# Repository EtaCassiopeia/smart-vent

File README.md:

# smart-vent

Per-room HVAC vent control. Each vent has a small XIAO ESP32-C6 board driving an SG90
hobby servo that opens or closes a louver. The board joins a Thread mesh hosted by a
Raspberry Pi and exposes itself as a Matter **Window Covering** device. Home Assistant
runs on the same Pi and is the user-facing controller — you toggle the vent in the HA UI
or in a HA automation, and the command travels over Matter-over-Thread to the device,
which moves the servo.

The project is **Matter-over-Thread only**. There is no Wi-Fi path on the device, and no
cloud dependency. The Pi is the entire backend.

## Hardware

| Role | Part | Notes |
|------|------|-------|
| Hub | Raspberry Pi (any model with USB) | Runs three Docker containers: OTBR, matter-server, Home Assistant |
| Thread radio | SMLIGHT SLZB-07 USB dongle | CP210x USB-UART (`10c4:ea60`), enumerates as `/dev/ttyUSB0`. Used by OTBR as the Thread Radio Co-Processor |
| Vent MCU | Seeed XIAO ESP32-C6 | RISC-V chip with built-in 802.15.4 and BLE radios. Enumerates as `/dev/ttyACM0` (`303a:1001`) when plugged **directly** into the Pi — not through a USB hub |
| Actuator | SG90 servo | Signal on GPIO2 (XIAO D2 pin). 90° = vent closed, 180° = vent open |

## Architecture at a glance

```
   ┌─────────────────────── Raspberry Pi ──────────────────────────┐
   │                                                                │
   │  Home Assistant ── (WebSocket) ──► matter-server               │
   │       (:8123)                       (:5580)                    │
   │                                        │ BLE pairing           │
   │                                        ▼                       │
   │                                     BlueZ ─── (host BT)        │
   │                                        │                       │
   │                                        │ Matter ops over IPv6  │
   │                                        ▼                       │
   │                                     OTBR (OpenThread Border    │
   │                                           Router container)    │
   │                                        │                       │
   │                                        │ Thread (802.15.4)     │
   └────────────────────────────────────────┼───────────────────────┘
                                            │  ▲
                                  via SLZB-07 USB dongle
                                            │  │
                              ┌─────────────▼──┴────────────┐
                              │   XIAO ESP32-C6 (vent N)    │
                              │   Rust firmware + esp-matter│
                              │   GPIO2 ─► SG90 servo       │
                              └─────────────────────────────┘
```

## Where to look

- **[docs/handbook.md](docs/handbook.md)** — what the system is, how it works, why
  it's built the way it is. Read this top-to-bottom once. Covers Matter, Thread,
  the Pi services, the firmware internals, what happens during commissioning and
  on every replug.
- **[docs/dev-setup.md](docs/dev-setup.md)** — what to install on your own dev
  machine (Linux x86_64 recommended, Pi for deployment/validation, macOS as
  a secondary option) before touching firmware, the SD image, the Pi hub
  stack, the provisioning CLI, or the PCB tooling.
- **[docs/runbook.md](docs/runbook.md)** — step-by-step procedures for **developers**.
  How to set up the Pi from scratch, build the firmware, flash a new vent, commission
  it via HA, assign it to a room. Plus a symptom-driven troubleshooting matrix.
- **[docs/provider-runbook.md](docs/provider-runbook.md)** — step-by-step for
  **providers** assembling kits to ship to clients. Uses the
  `smart-vent-provision` CLI end-to-end: bake the SD card, flash + capture N
  vents, print stickers + quick-start, pack and ship. No source builds.
- **[docs/mobile-api.md](docs/mobile-api.md)** — API contract the smart-vent mobile
  app builds against (matter-server WS, HA REST, mDNS).
- **[docs/mobile-app-spec.md](docs/mobile-app-spec.md)** — screen-by-screen spec
  the Flutter team works from.

## Repo layout

```
firmware/
  vent-controller/                 ESP32-C6 firmware (Rust + ESP-IDF v5.2.3)
    src/                           Rust modules: main, matter, servo, state, identity, ...
    components/esp_matter_bridge/  C++ shim over esp-matter SDK
    sdkconfig.defaults             Non-default ESP-IDF kconfig
    partitions.csv                 nvs / phy_init / 3 MB factory app layout
  shared-protocol/                 vent-protocol crate (CBOR types, angle constants)
docs/
  handbook.md                      Conceptual reference
  runbook.md                       Step-by-step procedures
homeassistant/                     Example HA configs (scripts, automations,
                                   schedule helpers, Lovelace dashboard) for
                                   room/floor grouping and scheduling. Copy
                                   into ~/homeassistant/. See runbook §7.5.
tools/
  scripts/                         setup_otbr.sh, setup_ha.sh — reference Pi bring-up
  qr-generator/                    Renders printable QR PNGs from the boot-logged Matter payload
```

## Status

All firmware code lives on the `feature/matter-over-thread` branch. One vent has been
fully commissioned and verified end-to-end (HA → Close button → servo turns to 90°,
HA → Open → servo turns to 180°). The same firmware image can be flashed onto any
number of XIAO ESP32-C6 boards to add more vents — see the runbook.

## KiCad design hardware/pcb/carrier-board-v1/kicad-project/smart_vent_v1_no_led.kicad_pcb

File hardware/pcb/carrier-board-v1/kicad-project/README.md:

# KiCad project — placement clean, NOT routed, NOT fab-ready

Two boards here, one per LED variant (see
[`docs/battery-carrier-board.md` §2a](../../../../docs/battery-carrier-board.md#2a-led-indicator-optional)
for the tradeoff):

| | With LED | Without LED |
|---|---|---|
| Board | `smart_vent_v1.kicad_pcb` | `smart_vent_v1_no_led.kicad_pcb` |
| Project | `smart_vent_v1.kicad_pro` | `smart_vent_v1_no_led.kicad_pro` |
| DRC report | `drc_report.json` | `drc_report_no_led.json` |
| Build with | `python3 build_board.py` | `SMART_VENT_LED=0 python3 build_board.py` |

Each `.kicad_pcb` has a matching `.kicad_pro` — open that (or just the
`.kicad_pcb` directly, KiCad doesn't require the project file to open a
board standalone) so the net-class trace/via widths from
[§5](../../../../docs/battery-carrier-board.md#5-board-layout-rules)
persist between sessions instead of resetting to defaults: `Default`
(signals) at 0.25mm track / 0.5mm via, `Power` (VBAT, VBAT_RAW, SERVO_VCC,
GND) at 0.9mm track / 0.6mm via. The project files were hand-built from
KiCad's blank template (`pcbnew` scripting doesn't expose project creation)
— if KiCad ever rewrites them on save, that's expected and fine.

Both were generated by `build_board.py` (run against KiCad 10.0.4's bundled
`pcbnew` Python module — see the script for how to invoke it; it bypasses
the GUI-only netlist-import step, which modern KiCad no longer exposes to
scripting). It loads real footprints from KiCad's stock libraries where one
exists, places everything at resolved, collision-free coordinates (see
below), and wires nets per `../smart_vent_board.py`'s connectivity.
**No copper has been routed on either.**

## Placement: resolved (issue #46's DRC findings are fixed)

The original floorplan (`smart_vent_floorplan.svg`) got the *zoning* right
— left=signal, right=power, bottom=connectors — but the exact coordinates
didn't account for real footprint courtyard sizes, and at actual sizes
several parts collided: the THT slide switch substitute for SW1 (10.37mm
wide — much bigger than the small SMD pushbutton the floorplan was sized
around) and the THT radial cap substitute for C2 (8.59mm round, vs. the
small SMD electrolytic originally planned) were the two biggest culprits.

`nudge_apart.py` solves this: it builds the board, finds every pair of
overlapping courtyards (using real, post-rotation courtyard geometry), and
iteratively pushes them apart along whichever axis needs the smaller move,
holding U1/J2/the left analog cluster (R4/R5/R6/C1) fixed since they had no
DRC findings. It converges to the coordinates now hardcoded in
`build_board.py`'s `PLACE` dicts. One footprint needed a manual follow-up
the solver doesn't know about: **J2** (the servo header) had its last pad
landing past the board's bottom edge entirely at its original anchor
position (the footprint's "position" is pad 1, not its geometric center —
a 3-pin 2.54mm-pitch vertical header's last pad sits 5.08mm away from that
anchor) and separately collided with **U1**'s placeholder footprint, which
is a tall thin single-column header utterly unrepresentative of the real
XIAO module's shape (see #45) — J2 ended up shifted sideways in x to clear
U1's column, then up in y to clear the board edge by the required 0.5mm.

Re-running DRC after these fixes, on both variants:

| | With LED (before → after) | Without LED (before → after) |
|---|---|---|
| Shorts | 3 → **0** | 1 → **0** |
| Clearance violations | 1 → **0** | 1 → **0** |
| Courtyard overlaps | 8 → **0** | 5 → **0** |
| Board-edge clearance | (masked by the above) → **0** | (masked by the above) → **0** |

What's left in `drc_report*.json` is purely cosmetic: silkscreen reference
labels overlapping each other or clipped by the board edge/solder mask —
normal for default-placed footprint text once parts are packed this
tightly, fixed by dragging labels in the PCB editor, not a routing or
electrical concern.

## Footprints with no exact stock match (placeholders, need sourcing — issue #45)

**C2 is resolved** — `Capacitor_SMD:CP_Elec_6.3x5.4` exists after all; the
first pass's library search missed it (it's filed under
`Capacitor_SMD.pretty`, not a separate electrolytic library). It's now the
real footprint on both boards (courtyard 9.69×7.19mm — similar area to the
THT stand-in it replaced, not smaller as originally assumed; needed one
follow-up nudge to R2 to clear a new, smaller overlap once the real shape
went in). Two placeholders remain:

| Ref | Part | Stand-in used | What's actually needed |
|---|---|---|---|
| U1 | Seeed XIAO ESP32-C6 | generic 1×7 pin header | The official Seeed XIAO footprint (KiCad's stock libraries only ship `MCU_Seeed_ESP32C3`, not the XIAO carrier module). Source from Seeed's own KiCad library or via `easyeda2kicad` against the LCSC part. Its odd placeholder shape is also why J2 needed the manual nudge above — expect to revisit J2's exact position once the real footprint lands. |
| J1 | "SM-2P" battery connector | generic 1×2 pin header | The hobby-RC "JST-SM" 2-pin plug is not a real JST series (despite the name) and isn't in KiCad's `Connector_JST.pretty` (checked `JST_PH`/`JST_VH`/`JST_GH` series specifically — none match). Needs a footprint sourced from the connector's actual datasheet/LCSC listing (e.g. via `easyeda2kicad` against a specific part number once you've picked the exact connector to buy), or substitute a connector that *is* in-library and adjust the BOM. |

## What's left (tracked in #46)

Placement is clean; routing is not done. Next: route to the five rules in
[`../../../../docs/battery-carrier-board.md` §5](../../../../docs/battery-carrier-board.md#5-board-layout-rules)
(fat traces on the servo power loop, single star ground, etc.), apply the
net classes from the `.kicad_pro` files, run DRC again (should stay clean
on the electrical/courtyard front; clean up the cosmetic silkscreen
overlaps while you're in there), then plot Gerbers per §6.

## Gerbers (pipeline validation only — see the warning in each folder)

`gerbers-unrouted-with-led/` and `gerbers-unrouted-no-led/` are committed
Gerber + drill exports of these same two boards. **Do not send these to a
fab** — there's no copper routed, even though placement is now clean. They
exist to confirm the export pipeline produces the JLCPCB-compatible layer
set documented in the main doc's §6; each folder has its own README
repeating this warning and the exact `kicad-cli` commands used to generate
it, so they're trivially reproducible rather than load-bearing artifacts.

To regenerate either (or once a board is actually routed):

```bash
kicad-cli pcb export gerbers --output <dest>/ <board>.kicad_pcb
kicad-cli pcb export drill   --output <dest>/ <board>.kicad_pcb
```

Once routing is done, replace these with the actual fab-ready output and
drop "unrouted" from the directory names.

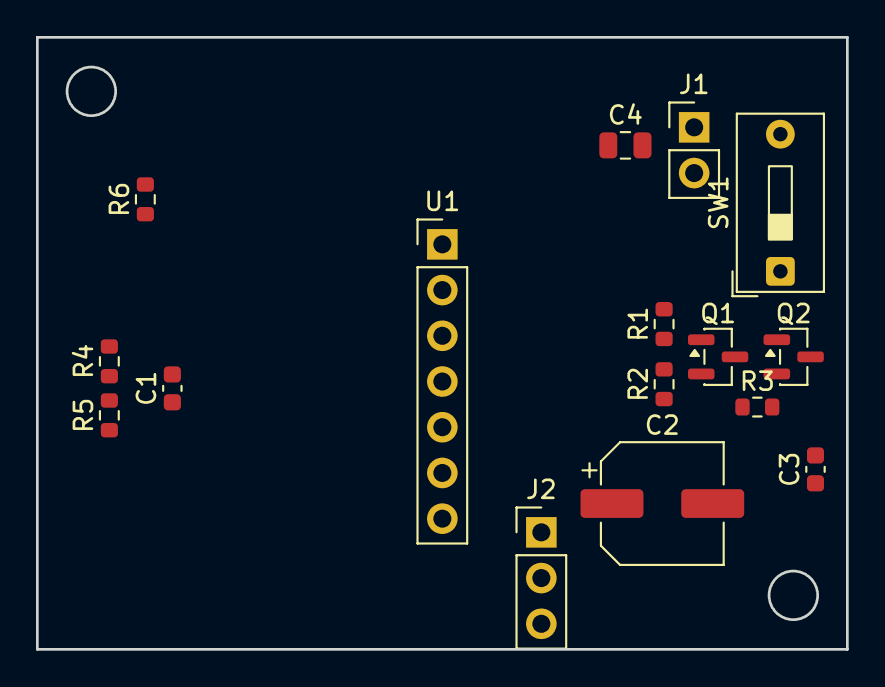
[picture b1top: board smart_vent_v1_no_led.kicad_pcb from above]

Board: 2 copper layers, 45.0 x 34.0 mm, 16 parts (0 on the bottom side), 8 nets, no tracks yet.

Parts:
C1, C3: C_0603_1608Metric
C2: CP_Elec_6.3x5.4
C4: C_0805_2012Metric
J1: PinHeader_1x02_P2.54mm_Vertical
J2: PinHeader_1x03_P2.54mm_Vertical
Q1, Q2: SOT-23
R1, R2, R3, R4, R5, R6: R_0603_1608Metric
SW1: SW_DIP_SPSTx01_Slide_9.78x4.72mm_W7.62mm_P2.54mm
U1: PinHeader_1x07_P2.54mm_Vertical

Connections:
GND: C1.2, C2.2, C3.2, C4.2, J1.2, J2.3, Q2.2, R5.2
NFET_GATE: Q2.1, R2.2, R3.1
PFET_GATE: Q1.1, Q2.3, R1.2
SERVO_SIG: J2.1, R6.2
SERVO_VCC: C2.1, C3.1, J2.2, Q1.3
VBAT: C4.1, Q1.2, R1.1, R4.1, SW1.2
VBAT_RAW: J1.1, SW1.1
VBAT_SENSE: C1.1, R4.2, R5.1

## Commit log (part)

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2026-02-19 Initial implementation of smart vent control system
    Rust ESP32-C6 firmware (servo, Thread, CoAP, deep sleep), Python hub
    service (device registry, group manager, OTBR discovery, CLI), device
    simulator for hardware-free testing, and Home Assistant custom component
    exposing vents as cover entities. Includes RFC, protocol spec, setup
    guides, and full test suites (5 Rust + 34 Python tests passing).
2026-02-19 Fix Mermaid diagrams for GitHub rendering
    - Remove special unicode chars that break GitHub Mermaid renderer
    - Remove curly braces and parentheses from message labels
    - Simplify stateDiagram to flat structure (GitHub has limited
    support for nested states and notes)
    - Move device lifecycle details into a companion table
2026-02-19 Add write-ahead recovery for interrupted servo moves
    If power is lost mid-move, the device now recovers correctly on
    reboot instead of snapping to a stale position.
    Protocol (event-sourcing inspired):
    1. Command received: save target + clear finalized flag in NVS
    2. Servo moves toward target
    3. Movement completes: save final angle + set finalized flag
2026-02-19 Fix RSSI reporting: use otThreadGetParentAverageRssi instead of RLOC16 (#9)
    get_rssi() was casting mRloc16 (a network address) to i8, returning
    garbage. Now calls otThreadGetParentAverageRssi() for the real value.
    Also wires ThreadManager into AppState so the health endpoint returns
    live RSSI instead of a hardcoded -50.
    Fixes #3
2026-02-19 Read power mode from NVS instead of hardcoding AlwaysOn (#11)
    Add get_power_mode/set_power_mode and get_poll_period/set_poll_period
    NVS accessors to DeviceIdentity. On boot, read power mode from NVS
    and fall back to AlwaysOn if unset, so battery-powered devices can
    enter SED mode without reflashing.
    Fixes #5
2026-02-19 Fix is_opening/is_closing to detect vent direction (#13)
    Both properties returned state=="moving" making them indistinguishable.
    Now the coordinator tracks the target angle from set_vent_position and
    includes it in poll data. The cover entity compares current angle vs
    target to determine if the vent is opening (target > current) or
    closing (target < current).
    Fixes #7
2026-02-21 Clarify Quick Start workflow in README
    Explain what the simulator does, lead with running tests as the
    primary verification step, and note that vent-hub discover requires
    a real Thread Border Router.
2026-02-21 Add .embuild to .gitignore
2026-02-21 Enable CoAP API for OpenThread MTD builds
    The OpenThread CoAP API (otCoapStart, etc.) is only enabled by default
    for FTD builds. Since our device runs as MTD, add a custom ESP-IDF
    component that sets OPENTHREAD_CONFIG_COAP_API_ENABLE=1 globally.
    The esp-idf-sys bindings header does not include openthread/coap.h, so
    otCoapStart is declared via extern "C" in coap.rs. The symbol is
    verified present in libopenthread.a.
2026-02-22 Fix OTBR script: remove -p flags conflicting with --network host
    Port mappings (-p) are ignored when --network host is used. All
    ports are exposed directly via host networking. Added verification
    step and a note explaining why docker ps shows no ports.
2026-02-22 Switch servo pin from GPIO6 to D2/GPIO2 for XIAO ESP32C6
    GPIO6 is on the MTCK bottom pad of the XIAO board, not accessible
    from the standard header pins. GPIO2 (D2) is on the header, supports
    PWM, and has no boot strapping conflicts. Updated wiring doc with
    full XIAO ESP32C6 pinout reference and ASCII wiring diagram.
2026-02-22 Update flash guide for XIAO ESP32C6 and release builds
    Replaced generic ESP32-C6 references with XIAO-specific device
    paths and notes. Added --release requirement (debug build exceeds
    partition size), explicit --port flag, and D2/GPIO2 servo pin in
    troubleshooting.
2026-02-22 Update docs to reflect actual boot output and Thread joining
    - flash-firmware.md: Update expected binary size (922KB) and serial
    output to match actual boot sequence including OpenThread mainloop
    and Thread role transition
    - commissioning.md: Update expected serial output to use default dev
    credentials (channel 15, OpenThreadDemo), add Role detached->child
    as the indicator of a successful join, add mainloop troubleshooting
2026-02-22 Wire CoAP resource handlers to OpenThread CoAP server
    Register a default CoAP handler via otCoapSetDefaultHandler that
    extracts URI path and method from incoming requests, delegates to
    route_request(), and sends back CBOR responses. Moves AppState into
    a Mutex<Option<AppState>> static so both the OT callback and main
    loop can access it safely.
2026-02-22 HA integration: read devices from hub DB, fix CBOR array handling
    - Coordinator reads device addresses from hub's SQLite database
    instead of static config entry list
    - Add db_path config option (default /config/devices.db)
    - Fix all CBOR response parsing to handle arrays (minicbor format)
    - Fix set_target to send CBOR array payload
    - Auto-add new device entities on coordinator updates
2026-02-22 Add vent entity icon (mdi:air-filter) and integration icon
    Set mdi:air-filter on cover entities and add a minimalist vent grille
    icon.png for the integration page.
2026-02-22 Fix Developer Tools nav paths and add service descriptions
    Developer Tools is in the sidebar on HA <2026.2 and under Settings on
    2026.2+. Use version-neutral paths. Add name/description fields to
    services.yaml so actions appear properly in the UI picker.
2026-02-23 Add BLE commissioning support and QR code generation
    Implement Matter commissioning via BLE:
    - Derive discriminator from EUI-64 lower 12 bits for unique BLE ads
    - Implement matter_bridge_get_pairing_code() and get_qr_payload()
    using CHIP SDK payload generators
    - Add tools/qr-generator/generate_qr.py for printable QR codes
    - Update flash-firmware.md with pairing info section
2026-02-23 Implement identify servo wiggle and onboarding documentation
    Firmware:
    - matter.rs: Implement on_identify callback with servo wiggle (10 deg
    back and forth until identify stop is received)
    - state.rs: Add identify_mode and identify_restore_angle to AppState
    - main.rs: During identify mode, wiggle instead of committing position
    Documentation:
2026-03-03 Add Matter Server container to setup and docs
    The HA Matter integration requires python-matter-server running as a
    separate container (port 5580) for HA Container installs. Update
    setup_ha.sh to start it automatically, and document the requirement
    in the quick-start, HA Matter, and RPi setup guides.
2026-06-19 Add HA room/floor grouping, remove pre-Matter hub
    Replaces the legacy CoAP-era Python hub and custom HA integration with
    example HA configs (scripts, automations, schedule helpers, dashboard)
    that drive grouping and scheduling entirely through HA's native
    Floors/Areas + cover.* services. Documents the Floors -> Areas -> Devices
    workflow in runbook section 7 / 7.5 and handbook section 9.3.
2026-06-20 Remove leftover CoAP server from firmware (#32)
    Drops src/coap.rs (the OpenThread CoAP server), the
    components/ot_coap_config kconfig override that turned on
    OPENTHREAD_CONFIG_COAP_API_ENABLE, the minicbor dependency, and the
    CBOR-only request/response structs in vent-protocol that only the CoAP
    handlers used. main.rs now calls state::init_app_state directly to
    publish the shared AppState in place of register_coap_resources.
2026-06-20 Add CI workflow for firmware build + release artifacts (#33)
    GitHub Actions workflow that builds the vent-controller firmware on PRs
    and pushes to main, and publishes release artifacts on firmware-v* tags.
    Outputs per release:
    - bootloader.bin / partition-table.bin / vent-controller.bin (matching
    the espflash piecemeal flash flow in runbook section 5.3)
    - vent-controller-merged.bin (single-image flash, no flag wrangling)
2026-06-20 Add smart-vent-provision CLI: flash + labels + kit-card
    Provider-side Python tool that pulls a tagged firmware release from
    GitHub Releases (sha256-verified against the manifest), drives espflash
    to write the bundle to each board interactively, and reads the post-boot
    serial log to capture each board's EUI-64, Matter QR payload, and manual
    pairing code into a per-kit inventory.json. Then renders an Avery 5160
    sticker sheet (one QR per vent) and a one-page client quick-start card.
2026-06-20 Add provision CLI build/test/release workflow (#37)
    Mirrors the firmware workflow shape but for tools/provision/:
    - PRs and main pushes that touch tools/provision/** run pytest, build
    the wheel + sdist, and upload them as a 14-day GitHub Actions build
    artifact.
    - Tags matching provision-v* additionally publish the wheel + sdist
    to a GitHub Release via softprops/action-gh-release.
2026-06-20 Add first-boot AP-mode WiFi onboarding wizard (step 4 of PR B)
    Custom Flask wizard rather than comitup/RaspiWiFi (rationale in
    pi/firstboot/README.md):
    - Branded SSID smart-vent-setup-<short-eui> matching the kit-card
    - Keeps NetworkManager as the runtime, not a network stack swap
    - ~250 LOC of one Python file; small integration surface
    Behaviour:
2026-06-21 Run sd-image bake on PRs that touch sd-image/ or pi/
    GH only registers workflow_dispatch handlers from the default branch,
    so a brand-new workflow can't be dispatched against a feature branch
    until it lands on main. Add pull_request triggers so PR #39 itself
    fires the bake, same pattern as firmware.yml and provision.yml.
    Path filters scope it to changes that actually affect the image.
2026-06-21 Find a populated rootfs from earlier stage instead of blindly copying PREV
    On the 2026-06-18 pi-gen tag, stage-smart-vent runs but
    work/stage2/rootfs is empty by the time we get there (the upstream
    stages must rely on something we don't see; copy_previous succeeds
    but only rsyncs the empty dir). Workaround: scan PREV_ROOTFS_DIR,
    work/stage2/rootfs, work/stage1/rootfs, work/stage0/rootfs in order
    and rsync from the first one that has a populated /etc + /usr. Also
2026-06-21 Let pi-gen use default WORK_DIR/DEPLOY_DIR
    The bake completed end-to-end and exported the .img.xz, but
    build-docker.sh's final cleanup step runs
    rsync -av work/*/build.log deploy/
    which expects work/<IMG_NAME>/build.log. With our explicit
    WORK_DIR=/pi-gen/work the log lives at work/build.log (one
    level shallower) and the glob expands to nothing, making rsync
2026-06-21 PR C: SD card image bake (pi-gen + QEMU) (#39)
    Bakes a Raspberry Pi OS Lite image with the smart-vent runtime
    pre-installed, so the provider can dd it to an SD card and ship.
    Stage layout follows pi-gen's native substage pattern (re-uses
    pi/install.sh's logic — apt installs via 00-packages, file copies
    via 01-run.sh, systemctl enable via 03-enable-services chroot):
    sd-image/config IMG_NAME, RELEASE=bookworm, ...
2026-06-21 Document the mobile-app contract + screen spec
    Workstream 6 of the deployment plan defined a separate Flutter repo
    (smart-vent-app) for the client mobile app. This repo doesn't build
    the app, but it owns the contract — what the app talks to on the
    hub, and what each screen needs to do.
    docs/mobile-api.md
    - Hub endpoints (matter-server WS at :5580, HA REST at :8123,
2026-06-21 Add docs/provider-runbook.md
    Closes the documentation gap surfaced by the deployment audit:
    the existing runbook (docs/runbook.md) is dev-focused — it talks
    about cargo build, espflash by hand, hand-typed docker compose. It
    has zero references to smart-vent-provision.
    A provider who reads it today would do all the work manually
    instead of using the CLI we shipped in PR #36 / #41.
2026-06-22 Make the carrier board's status LED optional; commit Gerbers for pipeline validation
    Splits the carrier board into two parallel variants (with-LED and
    no-LED), generated from the same smart_vent_board.py via a
    SMART_VENT_LED toggle, so the LED can be picked based on whether the
    locate/status feedback is worth its small continuous idle draw on the
    3V3 rail. Re-verified both with KiCad: dropping the LED also resolves
    most of the worst placement cluster DRC found in #46 (3 shorts -> 1,
